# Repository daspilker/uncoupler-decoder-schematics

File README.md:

Uncoupler Decoder
=================

This repository contains schematics and PCB design files for an decoder for the Märklin Digital system. The decoder has only one output and is well suited for uncoupler tracks.

These files have been created with the [EAGLE](http://www.cadsoftusa.com/) PCB software.

The PCB design meets the specifications of [OSH Park](http://oshpark.com/) community PCB order.

Bill Of Materials
-----------------

* **B1** RECT BRIDGE GPP 50V 1A DFS (DigiKey 641-1344-5-ND)
* **S1** SWITCH TAPE SEAL 9 POS SMD (DigiKey CT2199LPST-ND)
* **IC1** IC MCU AVR 2K FLASH 20SOIC (DigiKey ATTINY2313-20SU-ND)
* **IC2** IC VREG 100MA 5V SOT-89 (DigiKey MC78L05ACHXCT-ND)
* **C1** CAPACITOR TANT .10UF 35V 10% SMD (DigiKey 399-3676-1-ND)
* **C2** CAPACITOR TANT .33UF 35V 10% SMD (DigiKey 399-3693-1-ND)
* **C3** CAPACITOR TANT 10UF 25V 10% SMD (DigiKey 399-3734-1-ND)
* **D3** DIODE 75V 150MA SOD323F (DigiKey 1N4148WSFSCT-ND)
* **T1** TRANS NPN DARL 120V SOT23F-3 (DigiKey ZXTN04120HFFCT-ND)
* **R1** RES 270K OHM 1/8W 1% 0805 SMD (DigiKey RHM270KCCT-ND)
* **R2** RES 10.0K OHM 1/8W 1% 0805 SMD (DigiKey RHM10.0KCCT-ND)
* **R3** RES 4.70K OHM 1/8W 1% 0805 SMD (DigiKey RHM4.70KCCT-ND)

License
-------

Copyright 2012 Daniel A. Spilker

Licensed under the Apache License, Version 2.0 (the "License");
you may not use this file except in compliance with the License.
You may obtain a copy of the License at

    http://www.apache.org/licenses/LICENSE-2.0

Unless required by applicable law or agreed to in writing, software
distributed under the License is distributed on an "AS IS" BASIS,
WITHOUT WARRANTIES OR CONDITIONS OF ANY KIND, either express or implied.
See the License for the specific language governing permissions and
limitations under the License.

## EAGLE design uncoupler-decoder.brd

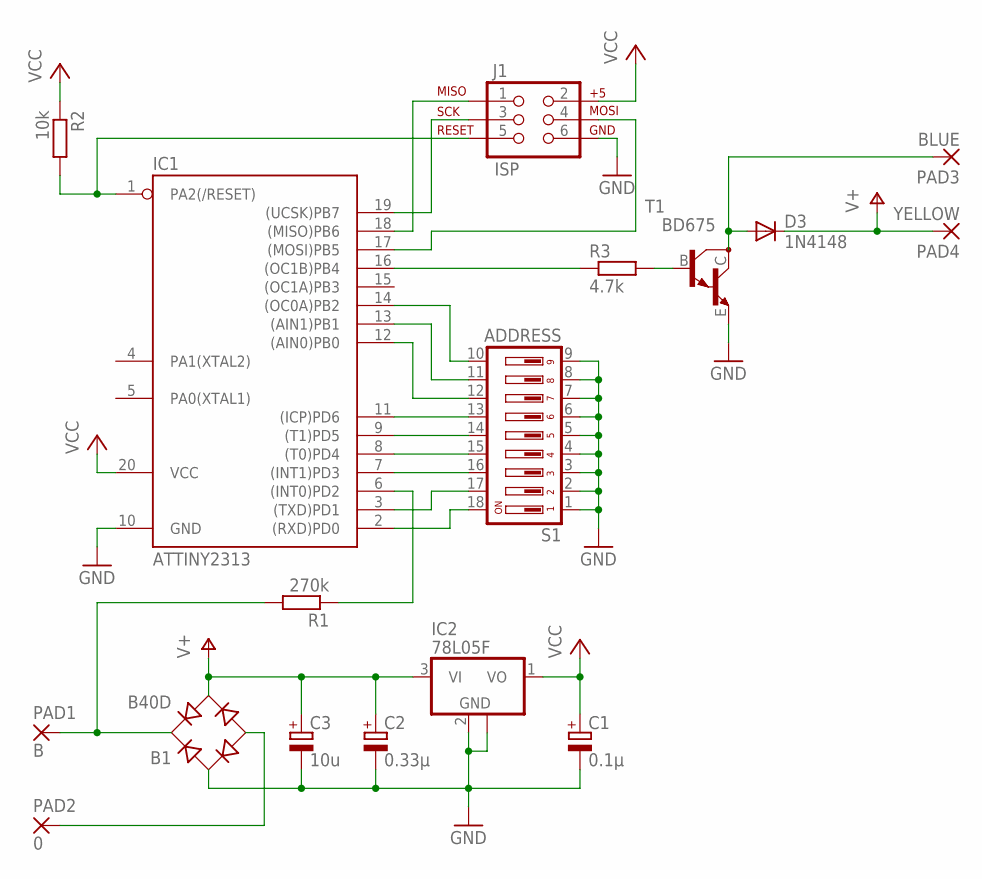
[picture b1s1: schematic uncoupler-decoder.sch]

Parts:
B1: B40D; B40S
C1: 0.1µ; A/3216-18R
C2: 0.33µ; A/3216-18R
C3: 10u; CT6032
D3: 1N4148; SOD323-R
IC1: ATTINY2313; SO20L$
IC2: 78L05F; SOT89
J1: ISP; ISP-ADAPTER-SMD
PAD1: B; SMD1,27-2,54
PAD2: 0; SMD1,27-2,54
PAD3: BLUE; SMD1,27-2,54
PAD4: YELLOW; SMD1,27-2,54
R1: 270k; R0805
R2: 10k; R0805
R3: 4.7k; R0805
S1: ADDRESS; CTS-219-09
T1: BD675; SOT23-BEC

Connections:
B: B1.+, PAD1.1, R1.2
GND: B1.AC1, C1.-, C2.-, C3.-, IC1.10 (GND), IC2.2 (GND), IC2.2@1 (GND), J1.6, S1.1, S1.2, S1.3, S1.4, S1.5, S1.6, S1.7, S1.8, S1.9, T1.E
unnamed: R3.2, T1.B
unnamed: IC1.11 ((ICP)PD6), S1.13
unnamed: IC1.9 ((T1)PD5), S1.14
unnamed: IC1.1 (PA2(/RESET)), J1.5, R2.2
unnamed: IC1.8 ((T0)PD4), S1.15
unnamed: IC1.7 ((INT1)PD3), S1.16
unnamed: B1.-, PAD2.1
unnamed: IC1.16 ((OC1B)PB4), R3.1
unnamed: D3.A, PAD3.1, T1.C
unnamed: IC1.18 ((MISO)PB6), J1.1
unnamed: IC1.3 ((TXD)PD1), S1.17
unnamed: IC1.19 ((UCSK)PB7), J1.3
unnamed: IC1.17 ((MOSI)PB5), J1.4
unnamed: IC1.14 ((OC0A)PB2), S1.10
unnamed: IC1.13 ((AIN1)PB1), S1.11
unnamed: IC1.12 ((AIN0)PB0), S1.12
unnamed: IC1.2 ((RXD)PD0), S1.18
unnamed: IC1.6 ((INT0)PD2), R1.1
V+: B1.AC2, C2.+, C3.+, D3.C, IC2.3 (VI), PAD4.1
VCC: C1.+, IC1.20 (VCC), IC2.1 (VO), J1.2, R2.1

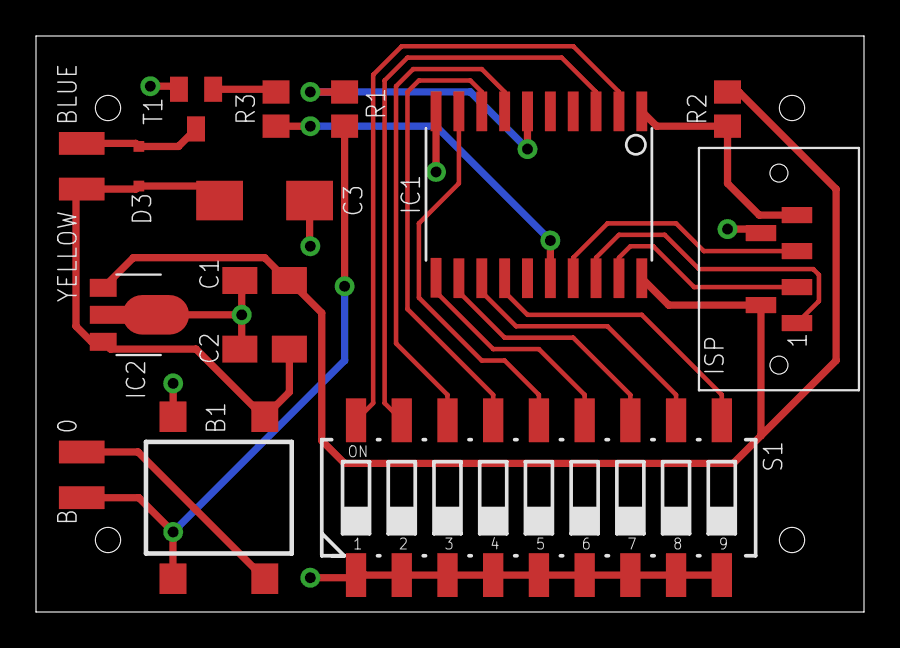
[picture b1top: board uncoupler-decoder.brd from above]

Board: 2 copper layers, 46.0 x 32.0 mm, 17 parts (0 on the bottom side), 22 nets.

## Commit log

2013-12-20 ignore CAM processor output

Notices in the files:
uncoupler-decoder.brd:
(c) 2010
